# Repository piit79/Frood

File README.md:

# The Frood

The Frood is a high-performance _and_ affordable Pro Micro drop-in replacement based on a Raspberry Pi RP2040. It is physically and electrically compatible with Elite-C/nice!nano as much as possible.

It follows the [SparkFun Pro Micro RP2040](https://www.sparkfun.com/products/18288) pinout with 5 more pins (GPIO12-GPIO16) added along the bottom edge (like on Elite-C), and USB data lines broken out in the top corners.

## Features

* Powerful dual-core Raspberry Pi RP2040 MCU
* 4 MB of on-board flash memory
* Only 3.2 mm thick thanks to a mid-mounted USB-C socket
* 500 mA linear regulator and resettable fuse
* Combined Pro Micro / Elite-C / nice!nano / SparkFun Pro Micro RP2040 compatible pinout
* 5 more I/O pins (GPIO12-GPIO16) added along the bottom edge
* 2 more I/O pins (GPIO10, GPIO11) can be converted from left-hand side GND pins by cutting a jumper
* 23-25 total available digital pins for a maximum of 11x12 = 132 (or even 12x13 = 156) switches
* 4 pins configurable as analogue inputs
* USB D+/D- broken out for use with an external USB socket/daughterboard
* USB power sensing on GPIO19 for split keyboard side detection
* UF2 bootloader for drag & drop programming with no extra software required
* Orange indicator LED on pin GPIO17
* Now with [official CircuitPython support](https://circuitpython.org/board/42keebs_frood/)

## Availability

The Frood is available from [42keebs.eu](https://42keebs.eu/shop/parts/controllers/frood-rp2040-pro-micro-controller/).

## Revision history

**Rev9** (03/01/2024)
* Allows converting left-hand side GND pins into GPIO pins (GPIO10, GPIO11) by cutting PCB jumpers
* VBUS IN/OUT solder jumper dropped, the RAW pin is now connected to VBUS after a Schottky diode/input of linear regulator before a resettable fuse
* Uses a different (but equivalent) USB-C socket due to component shortage
* Routing and silkscreen tweaks/improvements

**Rev8** (10/10/2023)
* Add a 2-way solder jumper to select VBUS OUT or VBUS IN on the RAW pin
* Use orange indicator LED again

**Rev7** (23/06/2023)
* Use a different 4 MB flash chip (Winbond W25Q32JVUUIQ) which will hopefully not need a special config
* Use a higher-quality Panasonic reset/boot switches
* Some routing tweaks
* Bug: uses red indicator LED by mistake

**Rev6** (28/12/2022)
* Use a 4 MB (32 Mbit) flash chip (needs a special configuration in QMK `config.h`: `#define RP2040_FLASH_GD25Q64CS`)
* Tweak a few tracks

**Rev5** (26/10/2022)
* Improve USB socket position to match nice!nano
* Add BOOT/RESET pads on the bottom of the PCB (when the buttons are not accessible)
* Use a smaller crystal to gain some valuable space
* Add an orange indicator LED on pin GPIO17 (inspired by the [0xB2](https://github.com/plut0nium/0xB2))

**Rev4** (28/09/2022) - **Confirmed working**
* Use a 2 MB flash with correct supply voltage rating
* Switch to GT-USB-7014C USB-C socket and a standard 1.6 mm PCB
* Improve pin labels
* Improve routing

**Rev3** (18/08/2022) - **DO NOT USE!**
* Rename to "Frood"
* Use HRO-TYPE-C-31-M-14 for a fully mid-mounted socket with a 1.0 mm PCB
* Use 500 mA fuse instead of 350 mA one
* Improve layout (move USB termination resistors closer to MCU)
* Still uses the same flash chip with an incorrect supply voltage (1.8-2.6 V)

**Rev2** (16/08/2022) - **DO NOT USE!**
* Rename to "PiMicro2040"
* Fix crystal routing
* Use Elite-C/nice!nano-like outline
* Use mid-mounted USB-C connector (HRO-TYPE-C-31-M-13)
* Use a "standard" Sparkfun Pro Micro-compatible pinout
* Add 350 mA resettable fuse
* Add VBUS sensing
* Break-out USB data lines
* Contains a critical error - flash chip with an incorrect supply voltage (1.8-2.6 V)

**Rev1** (08/08/2022) - **DO NOT USE!**
* Initial version with a top-mounted USB-C socket, a shorter outline and a custom pinout
* Contains a critial error - incorrect crystal routing due to a mismatch between a 2-pin symbol and a 4-pin footprint

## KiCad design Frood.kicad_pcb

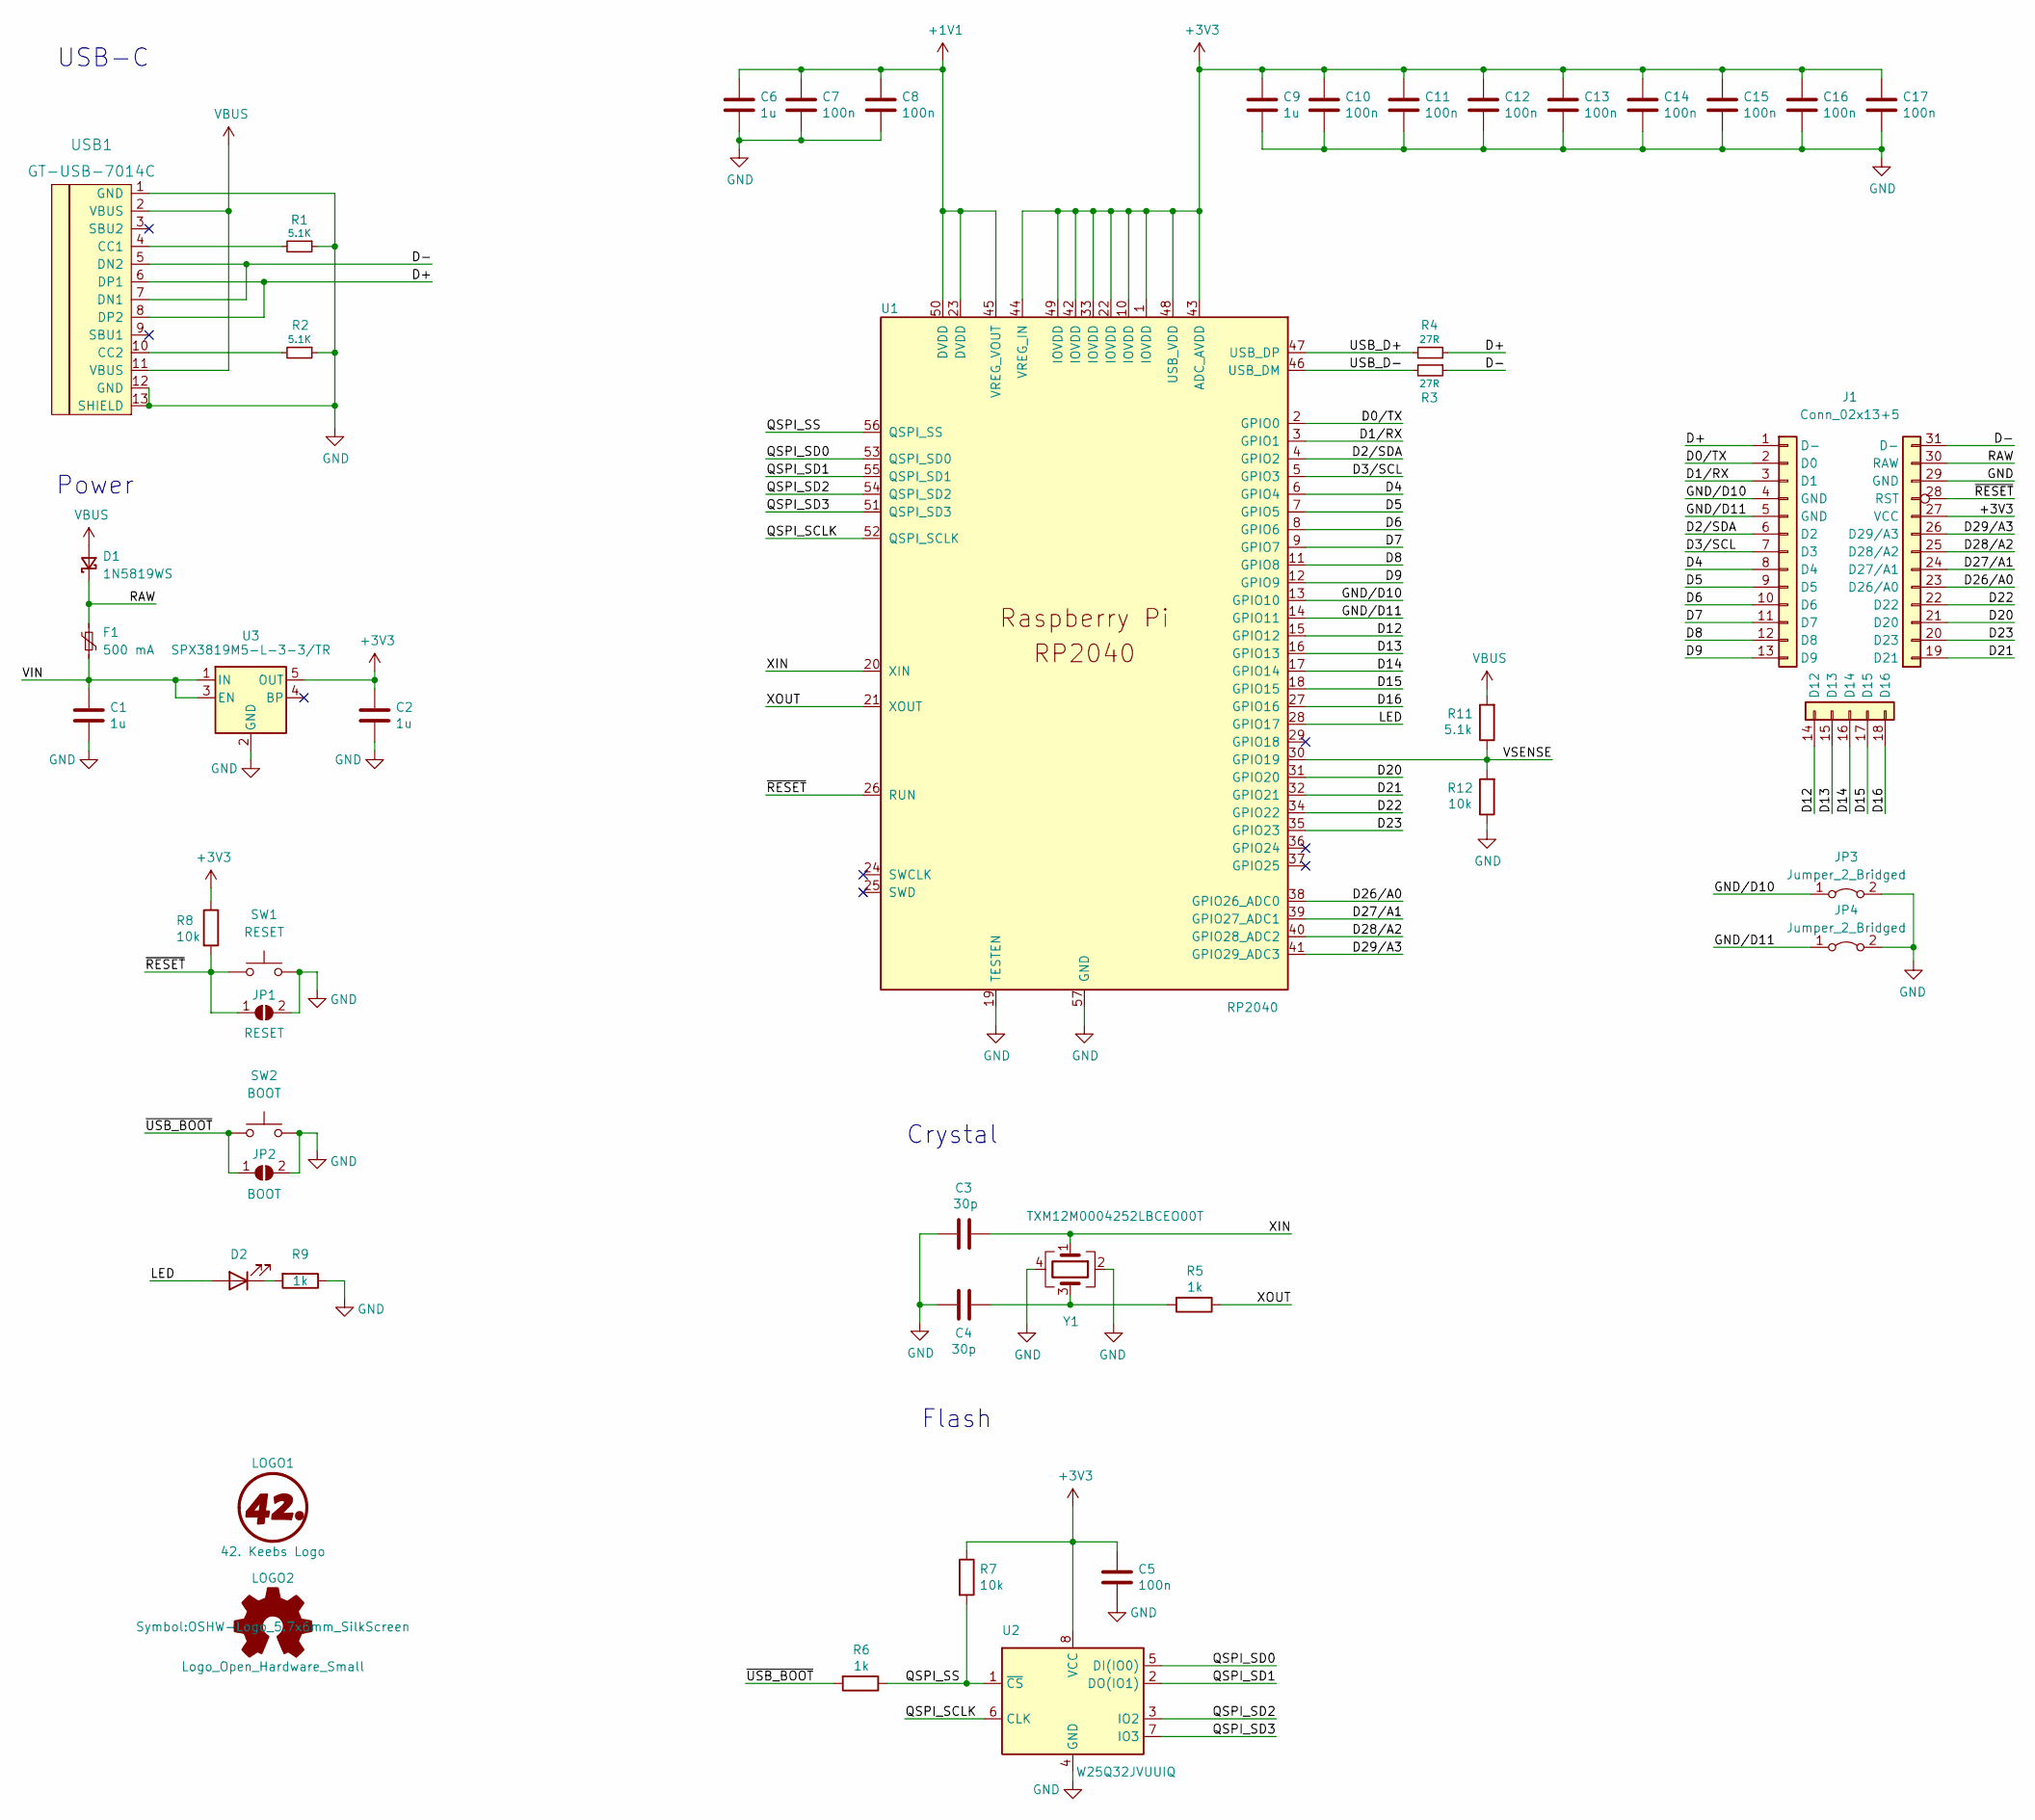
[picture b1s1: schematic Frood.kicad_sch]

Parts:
C1, C2, C6, C9: 1u; C_0402_1005Metric
C3, C4: 30p; C_0402_1005Metric
C5, C7, C8, C10, C11, C12, C13, C14, C15, C16, C17: 100n; C_0402_1005Metric
D1: 1N5819WS; D_SOD-323F
D2: LED; LED_0402_1005Metric
F1: 500 mA; R_0805_2012Metric
J1: Conn_02x13+5; PinHeader_2x13+5_P2.54mm_Vertical_Frood
JP1: RESET; SolderJumper-2_P1.3mm_Open_RoundedPad1.0x1.5mm
JP2: BOOT; SolderJumper-2_P1.3mm_Open_RoundedPad1.0x1.5mm
JP3, JP4: Jumper_2_Bridged; SolderJumper-2_P0.8mm_Bridged_RoundedPad0.5x1mm
LOGO1: 42. Keebs Logo; 42Keebs-icon-10mm-SilkS
LOGO2: Logo_Open_Hardware_Small; OSHW-Logo_5.7x6mm_SilkScreen
R1, R2: 5.1K; R_0402_1005Metric
R3, R4: 27R; R_0402_1005Metric
R5, R6, R9: 1k; R_0402_1005Metric
R7, R8, R12: 10k; R_0402_1005Metric
R11: 5.1k; R_0402_1005Metric
SW1: RESET; SW_SPST_CK_KXT3
SW2: BOOT; SW_SPST_CK_KXT3
U1: RP2040; RP2040-QFN-56
U2: W25Q32JVUUIQ; USON-8_4x3mm_P0.8mm
U3: SPX3819M5-L-3-3/TR; SOT-23-5
USB1: GT-USB-7014C; Molex-216990_GCT-USB45xx_HRO-TYPE-C-31-M-13x-Frood
Y1: TXM12M0004252LBCEO00T; Crystal_SMD_2520-4Pin_2.5x2.0mm

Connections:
+1V1: C6.1, C7.1, C8.1, U1.23 (DVDD), U1.45 (VREG_VOUT), U1.50 (DVDD)
+3V3: C2.1, C5.1, C9.1, C10.1, C11.1, C12.1, C13.1, C14.1, C15.1, C16.1, C17.1, J1.27 (VCC), R7.1, R8.1, U1.1 (IOVDD), U1.10 (IOVDD), U1.22 (IOVDD), U1.33 (IOVDD), U1.42 (IOVDD), U1.43 (ADC_AVDD), U1.44 (VREG_IN), U1.48 (USB_VDD), U1.49 (IOVDD), U2.8 (VCC), U3.5 (OUT)
/D0/TX: J1.2 (D0), U1.2 (GPIO0)
/D1/RX: J1.3 (D1), U1.3 (GPIO1)
/D2/SDA: J1.6 (D2), U1.4 (GPIO2)
/D3/SCL: J1.7 (D3), U1.5 (GPIO3)
/D4: J1.8 (D4), U1.6 (GPIO4)
/D5: J1.9 (D5), U1.7 (GPIO5)
/D6: J1.10 (D6), U1.8 (GPIO6)
/D7: J1.11 (D7), U1.9 (GPIO7)
/D8: J1.12 (D8), U1.11 (GPIO8)
/D9: J1.13 (D9), U1.12 (GPIO9)
/D12: J1.14 (D12), U1.15 (GPIO12)
/D13: J1.15 (D13), U1.16 (GPIO13)
/D14: J1.16 (D14), U1.17 (GPIO14)
/D15: J1.17 (D15), U1.18 (GPIO15)
/D16: J1.18 (D16), U1.27 (GPIO16)
/D20: J1.21 (D20), U1.31 (GPIO20)
/D21: J1.19 (D21), U1.32 (GPIO21)
/D22: J1.22 (D22), U1.34 (GPIO22)
/D23: J1.20 (D23), U1.35 (GPIO23)
/D26/A0: J1.23 (D26/A0), U1.38 (GPIO26_ADC0)
/D27/A1: J1.24 (D27/A1), U1.39 (GPIO27_ADC1)
/D28/A2: J1.25 (D28/A2), U1.40 (GPIO28_ADC2)
/D29/A3: J1.26 (D29/A3), U1.41 (GPIO29_ADC3)
/D+: J1.1 (D-), R4.1, USB1.6 (DP1), USB1.8 (DP2)
/D-: J1.31 (D-), R3.1, USB1.5 (DN2), USB1.7 (DN1)
/GND/D10: J1.4 (GND), JP3.1 (A), U1.13 (GPIO10)
/GND/D11: J1.5 (GND), JP4.1 (A), U1.14 (GPIO11)
/LED: D2.2 (A), U1.28 (GPIO17)
/QSPI_SCLK: U1.52 (QSPI_SCLK), U2.6 (CLK)
/QSPI_SD0: U1.53 (QSPI_SD0), U2.5 (DI(IO0))
/QSPI_SD1: U1.55 (QSPI_SD1), U2.2 (DO(IO1))
/QSPI_SD2: U1.54 (QSPI_SD2), U2.3 (IO2)
/QSPI_SD3: U1.51 (QSPI_SD3), U2.7 (IO3)
/QSPI_SS: R6.1, R7.2, U1.56 (QSPI_SS), U2.1 (~CS)
/RAW: D1.1 (K), F1.1, J1.30 (RAW)
/USB_D+: R4.2, U1.47 (USB_DP)
/USB_D-: R3.2, U1.46 (USB_DM)
/VIN: C1.1, F1.2, U3.1 (IN), U3.3 (EN)
/VSENSE: R11.1, R12.2, U1.30 (GPIO19)
/XIN: C3.1, U1.20 (XIN), Y1.1
/XOUT: R5.1, U1.21 (XOUT)
/~RESET: J1.28 (RST), JP1.1 (A), R8.2, SW1.1, U1.26 (RUN)
/~USB_BOOT: JP2.1 (A), R6.2, SW2.1
GND: C1.2, C2.2, C3.2, C4.2, C5.2, C6.2, C7.2, C8.2, C9.2, C10.2, C11.2, C12.2, C13.2, C14.2, C15.2, C16.2, C17.2, J1.29 (GND), JP1.2 (B), JP2.2 (B), JP3.2 (B), JP4.2 (B), R1.1, R2.1, R9.1, R12.1, SW1.2, SW2.2, U1.19 (TESTEN), U1.57 (GND), U2.4 (GND), U3.2 (GND), USB1.1 (GND), USB1.12 (GND), USB1.13 (SHIELD), Y1.2, Y1.4
unnamed: C4.1, R5.2, Y1.3
unnamed: D2.1 (K), R9.2
unnamed: R1.2, USB1.4 (CC1)
unnamed: R2.2, USB1.10 (CC2)
VBUS: D1.2 (A), R11.2, USB1.2 (VBUS), USB1.11 (VBUS)

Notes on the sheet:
Power
Crystal
Flash
USB-C

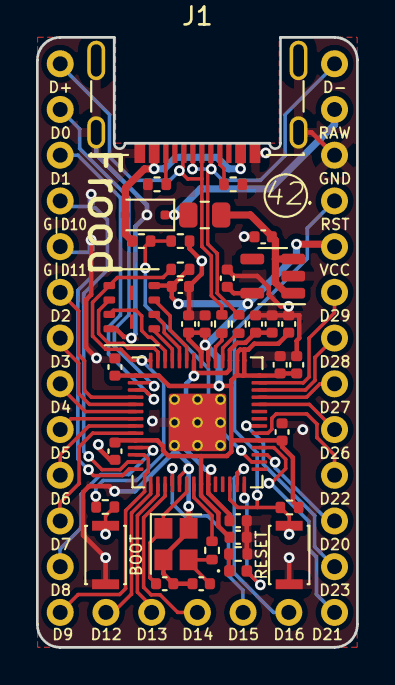
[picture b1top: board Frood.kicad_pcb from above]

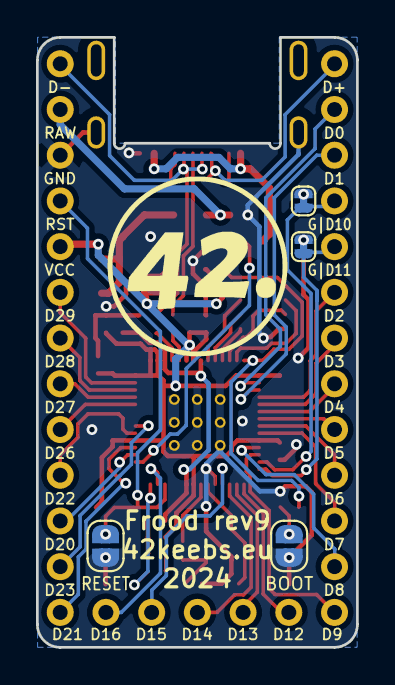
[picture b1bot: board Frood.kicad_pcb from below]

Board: 2 copper layers, 17.8 x 33.9 mm, 44 parts (5 on the bottom side), 51 nets.

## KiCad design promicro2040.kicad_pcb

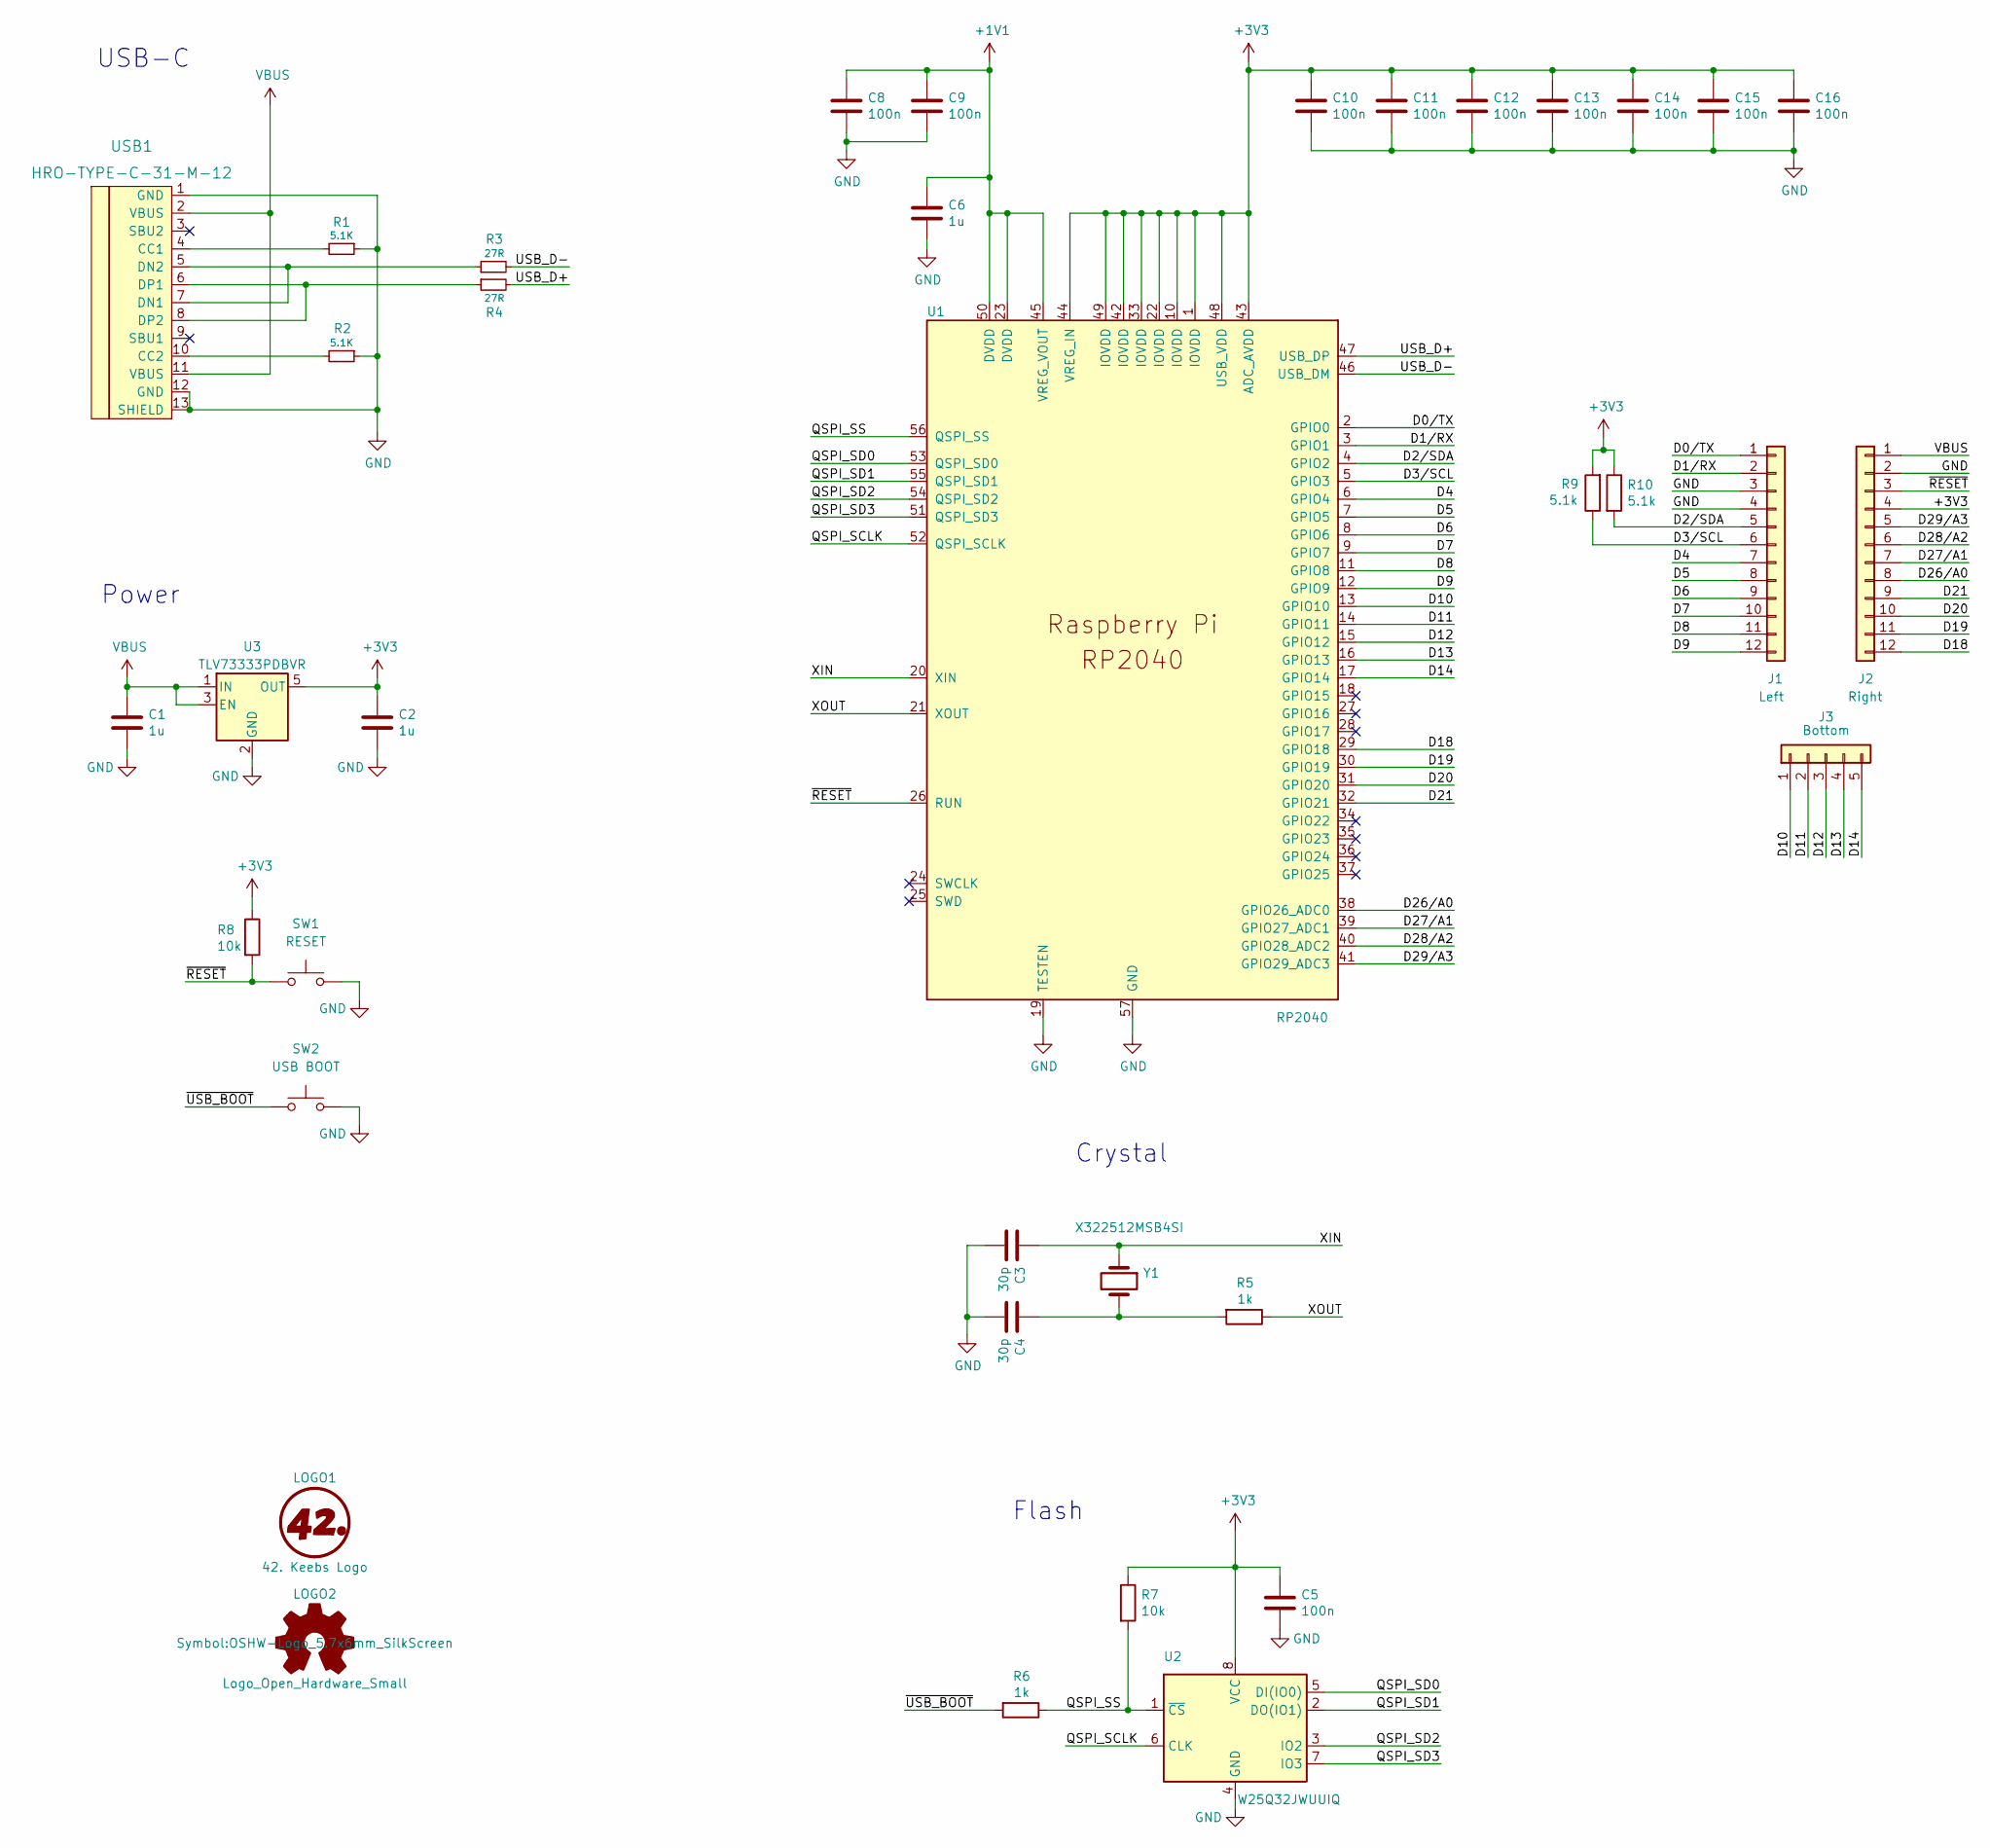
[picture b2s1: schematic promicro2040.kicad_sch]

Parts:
C1, C2, C6: 1u; C_0402_1005Metric
C3, C4: 30p; C_0402_1005Metric
C5, C8, C9, C10, C11, C12, C13, C14, C15, C16: 100n; C_0402_1005Metric
J1: Left; PinHeader_1x12_P2.54mm_Vertical_Plain
J2: Right; PinHeader_1x12_P2.54mm_Vertical_Plain
J3: Bottom; PinHeader_1x05_P2.54mm_Vertical_Plain
LOGO1: 42. Keebs Logo; 42Keebs-icon-10mm-SilkS
LOGO2: Logo_Open_Hardware_Small; OSHW-Logo_5.7x6mm_SilkScreen
R1, R2: 5.1K; R_0402_1005Metric
R3, R4: 27R; R_0402_1005Metric
R5, R6: 1k; R_0402_1005Metric
R7, R8: 10k; R_0402_1005Metric
R9, R10: 5.1k; R_0402_1005Metric
SW1: RESET; SW_SPST_CK_KXT3; LCSC C319433
SW2: USB BOOT; SW_SPST_CK_KXT3; LCSC C319433
U1: RP2040; RP2040-QFN-56
U2: W25Q32JWUUIQ; USON-8_4x3mm_P0.8mm; LCSC C2760370
U3: TLV73333PDBVR; SOT-23-5
USB1: HRO-TYPE-C-31-M-12
Y1: X322512MSB4SI; Crystal_SMD_3225-4Pin_3.2x2.5mm; PartNo C9002

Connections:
+1V1: C6.1, C8.1, C9.1, U1.23 (DVDD), U1.45 (VREG_VOUT), U1.50 (DVDD)
+3V3: C2.1, C5.1, C10.1, C11.1, C12.1, C13.1, C14.1, C15.1, C16.1, J2.4, R7.1, R8.1, R9.2, R10.1, U1.1 (IOVDD), U1.10 (IOVDD), U1.22 (IOVDD), U1.33 (IOVDD), U1.42 (IOVDD), U1.43 (ADC_AVDD), U1.44 (VREG_IN), U1.48 (USB_VDD), U1.49 (IOVDD), U2.8 (VCC), U3.5 (OUT)
/D0/TX: J1.1, U1.2 (GPIO0)
/D1/RX: J1.2, U1.3 (GPIO1)
/D2/SDA: J1.5, R10.2, U1.4 (GPIO2)
/D3/SCL: J1.6, R9.1, U1.5 (GPIO3)
/D4: J1.7, U1.6 (GPIO4)
/D5: J1.8, U1.7 (GPIO5)
/D6: J1.9, U1.8 (GPIO6)
/D7: J1.10, U1.9 (GPIO7)
/D8: J1.11, U1.11 (GPIO8)
/D9: J1.12, U1.12 (GPIO9)
/D10: J3.1, U1.13 (GPIO10)
/D11: J3.2, U1.14 (GPIO11)
/D12: J3.3, U1.15 (GPIO12)
/D13: J3.4, U1.16 (GPIO13)
/D14: J3.5, U1.17 (GPIO14)
/D18: J2.12, U1.29 (GPIO18)
/D19: J2.11, U1.30 (GPIO19)
/D20: J2.10, U1.31 (GPIO20)
/D21: J2.9, U1.32 (GPIO21)
/D26/A0: J2.8, U1.38 (GPIO26_ADC0)
/D27/A1: J2.7, U1.39 (GPIO27_ADC1)
/D28/A2: J2.6, U1.40 (GPIO28_ADC2)
/D29/A3: J2.5, U1.41 (GPIO29_ADC3)
/QSPI_SCLK: U1.52 (QSPI_SCLK), U2.6 (CLK)
/QSPI_SD0: U1.53 (QSPI_SD0), U2.5 (DI(IO0))
/QSPI_SD1: U1.55 (QSPI_SD1), U2.2 (DO(IO1))
/QSPI_SD2: U1.54 (QSPI_SD2), U2.3 (IO2)
/QSPI_SD3: U1.51 (QSPI_SD3), U2.7 (IO3)
/QSPI_SS: R6.1, R7.2, U1.56 (QSPI_SS), U2.1 (~CS)
/USB_D+: R4.2, U1.47 (USB_DP)
/USB_D-: R3.2, U1.46 (USB_DM)
/XIN: C3.1, U1.20 (XIN), Y1.1
/XOUT: R5.1, U1.21 (XOUT)
/~RESET: J2.3, R8.2, SW1.1, U1.26 (RUN)
/~USB_BOOT: R6.2, SW2.1
GND: C1.2, C2.2, C3.2, C4.2, C5.2, C6.2, C8.2, C9.2, C10.2, C11.2, C12.2, C13.2, C14.2, C15.2, C16.2, J1.3, J1.4, J2.2, R1.1, R2.1, SW1.2, SW2.2, U1.19 (TESTEN), U1.57 (GND), U2.4 (GND), U3.2 (GND), USB1.1 (GND), USB1.12 (GND), USB1.13 (SHIELD)
unnamed: C4.1, R5.2, Y1.2
unnamed: R1.2, USB1.4 (CC1)
unnamed: R2.2, USB1.10 (CC2)
unnamed: R3.1, USB1.5 (DN2), USB1.7 (DN1)
unnamed: R4.1, USB1.6 (DP1), USB1.8 (DP2)
VBUS: C1.1, J2.1, U3.1 (IN), U3.3 (EN), USB1.2 (VBUS), USB1.11 (VBUS)

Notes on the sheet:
Power
Crystal
Flash
USB-C

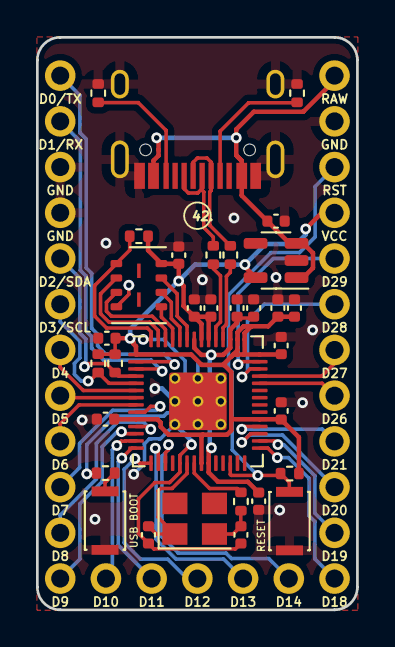
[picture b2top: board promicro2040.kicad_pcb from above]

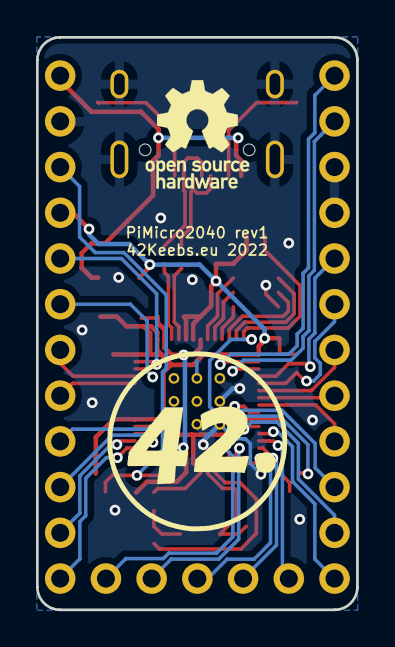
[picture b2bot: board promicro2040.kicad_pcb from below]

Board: 2 copper layers, 17.8 x 31.8 mm, 37 parts (2 on the bottom side), 44 nets.

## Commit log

2022-07-29 Add 42. Keebs KiCad library as a submodule
2022-07-29 Add the RP2040_minimal library
    Courtesy of https://datasheets.raspberrypi.com/rp2040/Minimal-KiCAD.zip
2022-07-29 Add ai03's Type-C.pretty KiCad library as a submodule
2022-08-08 Initial version with a top-mounted USB-C socket
2022-08-16 Update 42. Keebs KiCad library
2022-08-16 Remove foostan's kbd library as it's no longer used
2022-08-16 Bulk update to rev2
    * Rename to PiMicro2040
    * Fix critical error cause by 2-pin crystal symbol vs. 4-pin footprint
    * Use Elite-C/nice\!nano-like outline
    * Use mid-mounted USB-C connector
    * Use a "standard" Sparkfun Pro Micro-compatible pinout
    * Add 350 mA resettable fuse
2022-08-17 Rev3 update
    * Use HRO-TYPE-C-31-M-14
    * Use 500 mA fuse instead of 350 mA one
    * Improve layout (move USB termination resistors closer to MCU)
2022-08-17 Rename to Frood; use a 500 mA regulator; update README
2022-08-17 Add picture to README
2022-08-17 Fix the USB-C socket value; Use an in-stock 27R resistor
2022-08-18 Drop the forced I2C pull-up resistors; Add flash 3D model
2022-08-18 Move pin labels further inwards
2022-09-18 Update the 42. Keebs KiCad library
2022-09-28 Rev4 update
    * Use correctly-specced 16 Mbit QSPI flash
    * Switch to fully mid-mounted GT-USB-7014C USB-C socket and 1.6 mm PCB
    * Improve pin labels
    * Improve routing
    * Update the README with version history
2022-10-07 Improve USB socket position; add boot/reset pads on the bottom
2022-10-25 Rev5 update
    * Use a smaller crystal to get some valuable space back
    * Add an orange indicator LED on pin GPIO17
2022-10-25 Fix DRC violations when using round tracks
2023-06-27 Rev6 update
    * Use a 4 MB (32 Mb) flash chip instead
    * Minor routing fine-tuning
2023-06-27 Update .gitignore to exclude production files
2023-06-27 Rev7 update
    * Use a Winbond 4 MB flash chip
    * Use higher quality Panasonic reset/boot switches
    * A few routing tweaks
2023-10-10 Rev8 update
    * Add a 2-way solder jumper to select VBUS OUT or VBUS IN on the RAW pin
    * Use orange indicator LED again
2024-01-05 Rev9 update
    * Allows converting left-hand side GND pins into GPIO10,11 pins
    * Drop VBUS IN/OUT solder jumper, RAW pin now connected between the Schottky and fuse/regulator
    * Uses a different (but equivalent) USB-C socket
    * Routing and silkscreen tweaks/improvements
